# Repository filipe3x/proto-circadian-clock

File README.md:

# 🌅 Proto Circadian Clock

An ESP32-powered LED clock that simulates the natural solar light cycle to support healthy circadian rhythms. The display gradually transitions from warm red tones at sunrise/sunset to bright white at midday, mimicking natural daylight patterns.

## Features

- **Automatic Solar Simulation** - Real-time color temperature based on astronomical sun position
- **Red Light Therapy Mode** - Pure red light for evening relaxation
- **Multi-WiFi Support** - Connects to multiple configured networks with automatic fallback
- **Offline Operation** - Works without internet using RTC or internal clock
- **NTP Synchronization** - Keeps time accurate via internet time servers
- **Low Power** - Disconnects WiFi after sync to save energy
- **Startup Sound & Alerts** - Retro-style 8-bit chiptune sounds on boot (can be disabled via captive portal)

## Hardware Requirements

| Component | Specification |
|-----------|---------------|
| Microcontroller | ESP32 Dev Module (4MB Flash) |
| Display | P10 32×16 RGB LED Panel (HUB75, 1/4 scan, SMD3535) |
| RTC (Optional) | DS3231 module |
| Button | Momentary push button |
| Buzzer (Optional) | MLT-5030 piezo buzzer or similar (passive, 3V, 5×5mm) |
| Power | 5V 2A minimum |

## Wiring

### Pinout Absoluto ESP32 — Todos os GPIOs

```
┌─────────────────────────────────────────────────────────────────┐
│                    ESP32-WROOM-32E  PINOUT                      │
├───────┬──────────────┬──────────┬───────────────────────────────┤
│ GPIO  │ Função       │ Direção  │ Notas                        │
├───────┼──────────────┼──────────┼───────────────────────────────┤
│       │ ── HUB75 (Painel P10 RGB) ──                           │
│  4    │ LAT          │ Output   │ Latch                        │
│  5    │ C            │ Output   │ Row select bit 2             │
│ 12    │ G2           │ Output   │ Green lower                  │
│ 13    │ B2           │ Output   │ Blue lower                   │
│ 14    │ R2           │ Output   │ Red lower                    │
│ 15    │ OE           │ Output   │ Output Enable (active LOW)   │
│ 16    │ CLK          │ Output   │ Pixel clock                  │
│ 17    │ D            │ Output   │ Row select bit 3             │
│ 19    │ B            │ Output   │ Row select bit 1             │
│ 23    │ A            │ Output   │ Row select bit 0             │
│ 25    │ R1           │ Output   │ Red upper                    │
│ 26    │ G1           │ Output   │ Green upper                  │
│ 27    │ B1           │ Output   │ Blue upper                   │
├───────┼──────────────┼──────────┼───────────────────────────────┤
│       │ ── I2C (RTC + OLED) ──                                 │
│ 21    │ SDA          │ Bidi     │ DS3231 (0x68) + SSD1306 (0x3C) │
│ 22    │ SCL          │ Bidi     │ Barramento partilhado        │
├───────┼──────────────┼──────────┼───────────────────────────────┤
│       │ ── Input (partilhado — ver INPUT_MODE) ──              │
│ 34    │ ENC_A/BTN_A  │ Input    │ Pull-up 10kΩ ext. Encoder A ou Botão A │
│ 35    │ ENC_B/BTN_B  │ Input    │ Pull-up 10kΩ ext. Encoder B ou Botão B │
│ 36    │ BTN_L        │ Input    │ Pull-up 10kΩ ext. Exclusivo DevKit     │
│ 39    │ ENC_BTN/BTN_R│ Input    │ Pull-up 10kΩ ext. Enc Click ou Botão R │
├───────┼──────────────┼──────────┼───────────────────────────────┤
│       │ ── Outros ──                                           │
│  0    │ BOOT Button  │ Input    │ INPUT_PULLUP, modo cycle     │
│  2    │ LED_BUILTIN  │ Output   │ LED azul onboard             │
│ 18    │ BUZZER       │ Output   │ PWM → R 1kΩ → Q1 MMBT2222A  │
│ 33    │ VBUS_SENSE   │ Input    │ ADC1_CH5, deteção 20V        │
│  1    │ DEBUG TX     │ Output   │ UART0 TX (USB-UART)          │
│  3    │ DEBUG RX     │ Input    │ UART0 RX (USB-UART)          │
├───────┼──────────────┼──────────┼───────────────────────────────┤
│       │ ── Não disponíveis ──                                  │
│ 6-11  │ Flash SPI    │ —        │ Reservados internamente      │
│ 20    │ Não exposto  │ —        │ Indisponível na maioria dos devkits │
│ 24    │ Não existe   │ —        │ Não existe no ESP32          │
│ 28-31 │ Não expostos │ —        │ Não expostos em devkits      │
├───────┼──────────────┼──────────┼───────────────────────────────┤
│       │ ── Livre ──                                            │
│ 32    │ RESERVA      │ I/O      │ ADC1_CH4, touch — I2S DIN ou expansão │
└───────┴──────────────┴──────────┴───────────────────────────────┘
```

**Total: 28 GPIOs utilizados, 1 livre (GPIO 32), 10 indisponíveis.**

### Input Mode — GPIOs Partilhados

Os GPIOs 34, 35 e 39 servem dois modos de input (mesmo circuito elétrico):

```cpp
#define INPUT_MODE 0  // Click Wheel — encoder magnético AS5600 I2C (brilho + modo)
#define INPUT_MODE 1  // DevKit Buttons — 4 botões táteis (A/B/L/R)
```

Ver `DEVKIT_DISPLAY_BUTTONS.md` e `product/CLICK_WHEEL.md` para detalhes.

### ESP32 → P10 Panel (HUB75)

```
ESP32          P10 Panel
─────          ─────────
GPIO 25   →    R1
GPIO 26   →    G1
GPIO 27   →    B1
GPIO 14   →    R2
GPIO 12   →    G2
GPIO 13   →    B2
GPIO 23   →    A
GPIO 19   →    B
GPIO 5    →    C
GPIO 17   →    D
GPIO 4    →    LAT
GPIO 15   →    OE
GPIO 16   →    CLK
GND       →    GND
```

### I2C — RTC DS3231 + OLED SSD1306 (barramento partilhado)

```
ESP32          DS3231 (0x68)     SSD1306 (0x3C)
─────          ──────            ──────────────
GPIO 21   →    SDA          →    SDA
GPIO 22   →    SCL          →    SCL
3.3V      →    VCC          →    VCC
GND       →    GND          →    GND
```

> **Nota:** O OLED (SSD1306) é opcional, montado no verso da PCB (modo DevKit).
> Não conflitua com o RTC — endereços I2C diferentes.

### Button

```
GPIO 0    →    Button   →    GND
```

### Buzzer (Optional)

```
ESP32          Buzzer Circuit
─────          ──────────────
GPIO 18   →    R1 (1kΩ)   →   Base (NPN)
                               │
                               ├── Collector → Buzzer+ → 5V
                               │
                               └── Emitter → GND

D1 (1N4148) across Buzzer (cathode to +5V)
```

Recommended transistor: 2N2222 or BC547

**Note:** GPIO 18 is used because GPIO 6-11 are internally connected to the ESP32 flash SPI and unavailable.

## Software Dependencies

### ESP32 Board Package

In Arduino IDE, add this URL to **File → Preferences → Additional Board Manager URLs**:
```
https://espressif.github.io/arduino-esp32/package_esp32_index.json
```

Then install **esp32** by Espressif Systems via **Tools → Board → Boards Manager**.

> ⚠️ **Important:** Use **ESP32 Arduino 2.0.x** (tested with 2.0.14), NOT version 3.x.
> The ESP32-HUB75-MatrixPanel-I2S-DMA library has compatibility issues with ESP32 Arduino 3.x
> due to breaking changes in the ESP-IDF 5.x I2S and DMA APIs. Version 2.0.x uses ESP-IDF 4.4
> which provides stable support for HUB75 LED panels.

### Arduino Libraries

Install via **Sketch → Include Library → Manage Libraries**:

| Library | Version | Author | Description |
|---------|---------|--------|-------------|
| **ESP32-HUB75-MatrixPanel-I2S-DMA** | 3.0.x | mrcodetenz (mrfaptastic) | LED matrix driver |
| **RTClib** | 2.1.x | Adafruit | RTC DS3231 support |
| **Dusk2Dawn** | 1.0.x | DM Kishi | Solar calculations |
| **ESPAsyncWebServer** | 1.2.x | me-no-dev | Async web server for captive portal |
| **AsyncTCP** | 1.1.x | me-no-dev | Async TCP for ESP32 |

### Manual Installation

The P10 panel wrapper library (not in Library Manager):

```bash
cd ~/Arduino/libraries/
git clone https://github.com/filipe3x/P10_32x16_QuarterScan.git
```

## Configuration

### Location Settings

Edit these constants in `clock.ino`:

```cpp
// Your location (for solar calculations)
const float LATITUDE = 41.5362;    // Your latitude
const float LONGITUDE = -8.7813;   // Your longitude
const int TIMEZONE_OFFSET = 0;     // Hours from UTC

// Shift the solar cycle (e.g., -1 to wake up earlier)
const int SOLAR_OFFSET_HOURS = 1;
```

### WiFi Credentials

Copy `wifi_credentials.h.example` to `wifi_credentials.h` and add your networks:

```bash
cp wifi_credentials.h.example wifi_credentials.h
```

Then edit `wifi_credentials.h`:

```cpp
WiFiCredentials wifiNetworks[] = {
  {"YourNetwork1", "password1"},
  {"YourNetwork2", "password2"},
};
```

**Note:** `wifi_credentials.h` is ignored by git to keep your passwords private.

## Installation

1. Install [Arduino IDE](https://www.arduino.cc/en/software) with ESP32 board support
2. Install required libraries (see above)
3. Open `clock.ino`
4. Select board: **ESP32 Dev Module**
5. Set upload speed: **921600**
6. Configure your location and WiFi credentials
7. Upload to ESP32

## Usage

### Operating Modes

Press the button (GPIO 0) to cycle through modes:

| Mode | Description |
|------|-------------|
| **AUTO_SOLAR** | Automatic color based on sun position |
| **THERAPY_RED** | Constant red light for therapy/relaxation |
| **OFF** | Display turned off |

### Startup Sound

If buzzer is installed, the clock plays a retro-style 8-bit startup melody on boot. The sound can be:

- **Enabled/Disabled** via the captive portal web interface
- **Customized** with different chiptune melodies (NES/GameBoy style)
- **Future use** as alarm/notification sounds

The buzzer uses PWM to generate classic pulse wave tones with configurable duty cycles (12.5%, 25%, 50%) for authentic retro sound.

### Status Indicators (Boot)

| Color | Status |
|-------|--------|
| 🟢 Green | RTC + WiFi + NTP synced (perfect) |
| 🔵 Blue | WiFi + NTP synced (good) |
| 🟡 Yellow | RTC + WiFi, NTP failed |
| 🟣 Purple | RTC only, offline |
| 🟠 Orange | WiFi only, no valid time |
| 🔴 Red | Fully offline |

### Solar Color Schedule (Example: Winter, Portugal)

| Time | Elevation | Color | Brightness |
|------|-----------|-------|------------|
| 06:00 | -25° | Off | 0% |
| 07:30 | -12° | Deep red | 18% |
| 08:00 | -6° | Orange | 28% |
| 09:00 | 0° | Warm orange | 40% |
| 12:00 | 30° | Bright white | 100% |
| 18:00 | 0° | Warm orange | 40% |
| 21:00 | -12° | Deep red | 18% |
| 22:00 | -18° | Off | 0% |

## Troubleshooting

### Display not working
- Check 5V power supply (minimum 2A)
- Verify all HUB75 connections
- Ensure P10_32x16_QuarterScan library is installed

### RTC not detected
- System works without RTC (uses NTP)
- Check I2C connections (SDA=21, SCL=22)
- Verify 3.3V power (NOT 5V)
- Check CR2032 battery

### WiFi not connecting
- System works offline with RTC
- Check credentials in `wifiNetworks[]`
- Increase `WIFI_TIMEOUT_MS` for slow networks

### Wrong time/colors
- Verify `LATITUDE` and `LONGITUDE`
- Check `TIMEZONE_OFFSET` (0 for Portugal/UK)
- Adjust `SOLAR_OFFSET_HOURS` if needed

## Serial Monitor

Connect at **115200 baud** to see:
- Boot sequence and connectivity status
- Solar information (sunrise/sunset times)
- Elevation and color updates every 5 minutes
- Mode changes

## Roadmap

Potential future enhancements:

- **Dawn Simulator Mode** - Gradual wake-up light 30 min before alarm
- **Brightness Adjustment** - Manual or ambient sensor-based control
- **Web Interface** - Configuration via WiFi AP mode
- **Multiple Profiles** - Different settings per day of week
- **Home Assistant Integration** - MQTT control

## Authors

- **Filipe Marques** ([@filipe3x](https://github.com/filipe3x)) - Creator and maintainer
- **Claude** (Anthropic) - AI pair programming assistant

## License

MIT License - Feel free to use and modify.

## Contributing

Pull requests welcome! Please test on actual hardware before submitting.

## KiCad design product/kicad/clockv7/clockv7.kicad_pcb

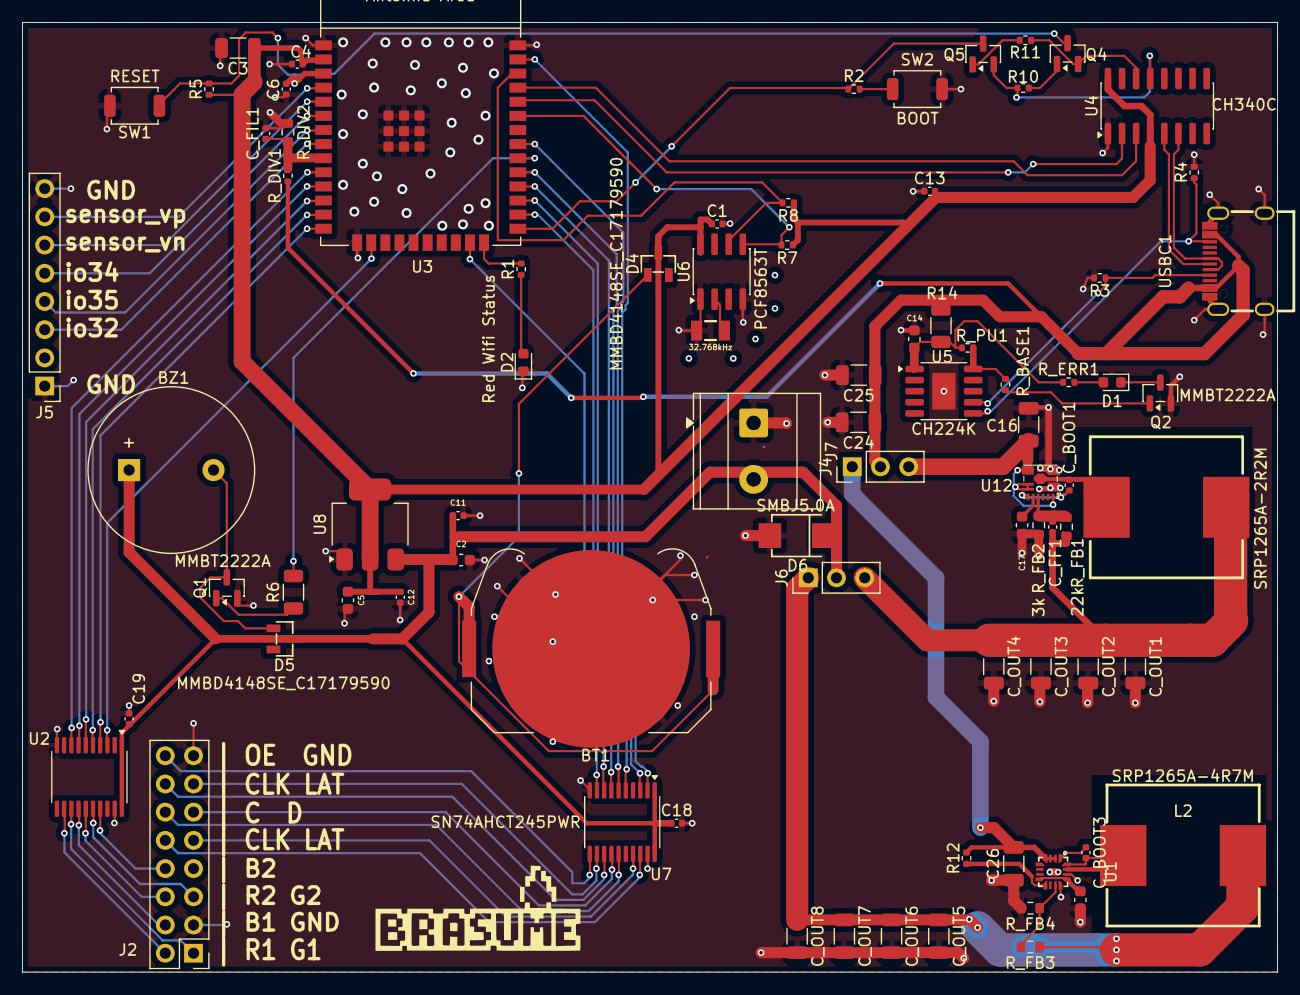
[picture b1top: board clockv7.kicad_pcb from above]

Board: 2 copper layers, 113.0 x 85.5 mm, 82 parts (0 on the bottom side), 76 nets.

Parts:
BT1: Battery_Cell; BatteryHolder_Keystone_3034_1x20mm
BZ1: Buzzer; Buzzer_14x9.5RM7.6
C1, C4, C6, C11, C12, C13, C18, C19: 100nF(50V); C_0402_1005Metric
C2: 10uF; C_0603_1608Metric
C3: 22uF(10V); C_1206_3216Metric
C5: 22uF; C_0603_1608Metric
C14, C17, C27: 1uF; C_0603_1608Metric
C16, C26: 10uF; C_1206_3216Metric
C24, C25: 22uF(25V); C_1206_3216Metric
C_BOOT1, C_BOOT3: 100nF(50V); C_0402_1005Metric
C_FF1: 22pF 50V; C_0402_1005Metric
C_FIL1: 100nF(50V); C_0402_1005Metric
C_OUT1, C_OUT2, C_OUT3, C_OUT4, C_OUT5, C_OUT6, C_OUT7, C_OUT8: 22uF(25V); C_1206_3216Metric
D1: LED_ERR; LED_0603_1608Metric
D2: Red Wifi Status; LED_0603_1608Metric
D4, D5: MMBD4148SE_C17179590; SOT-23-3_L2.9-W1.3-P0.95-LS2.4-BR
D6: SMBJ5.0A; SMB_L4.6-W3.6-LS5.4-RD
J2: GPIO +5V; PinHeader_2x08_P2.54mm_Vertical
J4, J6: Conn_01x03; PinHeader_1x03_P2.54mm_Vertical
J5: GPIO +3V3; PinHeader_1x08_P2.54mm_Vertical
J7: 3.5mm; TerminalBlock_Phoenix_MKDS-3-2-5.08_1x02_P5.08mm_Horizontal
L1: SRP1265A-2R2M; IND-SMD_L13.5-W12.5
L2: SRP1265A-4R7M; IND-SMD_L13.5-W12.5
Q1, Q2, Q4, Q5: MMBT2222A; SOT-23
R1: 330R; R_0402_1005Metric
R2: 100R; R_0402_1005Metric
R3, R4: 5.1k; R_0402_1005Metric
R5, R10, R11: 10k; R_0402_1005Metric
R6, R14: 1K; R_1206_3216Metric
R7, R8: 4.7k; R_0402_1005Metric
R12: 47k; R_0402_1005Metric
R_BASE1: 10k; R_0402_1005Metric
R_DIV1: 47k; R_0402_1005Metric
R_DIV2: 5.6k; R_0603_1608Metric
R_ERR1: 330R; R_0402_1005Metric
R_FB1, R_FB3: 22k; R_0603_1608Metric
R_FB2, R_FB4: 3k; R_0603_1608Metric
R_PU1: 10k; R_0402_1005Metric
SW1: RESET; SW_SPST_TS-1088-xR025
SW2: BOOT; SW_SPST_TS-1088-xR025
U1: SY8388ARHC; QFN-16_L2.5-W2.5-P0.45-TL-EP0.6
U2, U7: SN74AHCT245PWR; TSSOP-20_4.4x6.5mm_P0.65mm
U3: ESP32-WROOM-32EN8 (8MB); ESP32-WROOM-32E
U4: CH340C; SOIC-16_3.9x9.9mm_P1.27mm
U5: CH224K; SSOP-10-1EP_3.9x4.9mm_P1mm_EP2.1x3.3mm
U6: PCF8563T; SOIC-8_3.9x4.9mm_P1.27mm
U8: AMS1117-3.3; SOT-223-3_TabPin2
U12: SY8368AQQC; QFN-12_L3.0-W3.0-P0.45-TL-EP
USBC1: TYPE-C-31-M-12; USB-C_SMD-TYPE-C-31-M-12_1
Y1: 32.768kHz; Crystal_SMD_3.2x1.5mm

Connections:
5V_BUCK1: C_FF1.1, C_OUT1.1, C_OUT2.1, C_OUT3.1, C_OUT4.1, J6.3, L1.2, R_FB1.1
5V_BUCK2: C_OUT5.1, C_OUT6.1, C_OUT7.1, C_OUT8.1, J6.1, L2.2, R_FB3.1
5V_OUT: BZ1.1 (+), C2.1, C11.1, C18.1, C19.2, D5.3, D6.1 (K), J6.2, J7.2, U2.1 (DIR), U2.20 (VCC), U7.1 (DIR), U7.20 (VCC), U8.3 (VI)
20V_BUCK1: C16.1, J4.3, U12.4 (IN), U12.5 (IN), U12.6 (IN), U12.12 (EN)
20V_BUCK2: C26.2, J4.1, R12.2, U1.2 (IN), U1.3 (IN), U1.4 (IN)
20V_OUT: C24.1, C25.1, J4.2, R14.2, R_DIV1.1, USBC1.A4B9 (VBUS), USBC1.B4A9 (VBUS)
+3V3: C1.1, C3.1, C4.1, C5.1, C12.1, C13.2, D4.3, R5.1, R7.1, R8.1, U3.2 (VDD), U4.4 (V3), U4.16 (VCC), U6.8 (VDD), U8.2 (VO)
A: U3.37 (IO23), U7.2 (A1)
A_HUB75: J2.10, U7.18 (B1)
B: U3.31 (IO19), U7.3 (A2)
B1: U2.6 (A5), U3.12 (IO27)
B1_HUB75: J2.4, U2.14 (B5)
B2: U2.3 (A2), U3.16 (IO13)
B2_HUB75: J2.8, U2.17 (B2)
BOOT: Q5.3 (C), R2.1, U3.25 (IO0)
BUZZER: R6.2, U3.30 (IO18)
B_HUB75: J2.9, U7.17 (B2)
C: U3.29 (IO5), U7.5 (A4)
CC1: R3.1, U5.7 (CC1), USBC1.A5 (CC1)
CC2: R4.1, U5.6 (CC2), USBC1.B5 (CC2)
CLK: U3.27 (IO16), U7.7 (A6)
CLK_HUB75: J2.14, U7.13 (B6)
C_HUB75: J2.12, U7.15 (B4)
D: U3.28 (IO17), U7.6 (A5)
D+: U4.5 (UD+), USBC1.A6 (DP1), USBC1.B6 (DP2)
D-: U4.6 (UD-), USBC1.A7 (DN1), USBC1.B7 (DN2)
DTR: Q5.2 (E), R10.1, U4.13 (~DTR)
D_HUB75: J2.11, U7.14 (B5)
EN: C6.2, Q4.3 (C), R5.2, SW1.1 (A), U3.3 (EN)
FB1: C_FF1.2, R_FB1.2, R_FB2.1, U12.9 (FB)
FB2: R_FB3.2, R_FB4.1, U1.11 (FB)
G1: U2.7 (A6), U3.11 (IO26)
G1_HUB75: J2.1, U2.13 (B6)
G2: U2.4 (A3), U3.14 (IO12)
G2_HUB75: J2.5, U2.16 (B3)
GND: BT1.2 (-), C1.2, C2.2, C3.2, C4.2, C5.2, C6.1, C11.2, C12.2, C13.1, C14.2, C16.2, C17.2, C18.2, C19.1, C24.2, C25.2, C26.1, C27.1, C_FIL1.2, C_OUT1.2, C_OUT2.2, C_OUT3.2, C_OUT4.2, C_OUT5.2, C_OUT6.2, C_OUT7.2, C_OUT8.2, D2.1 (K), D6.2 (A), J2.3, J2.15, J5.1, J5.8, J7.1, Q1.2 (E), Q2.2 (E), R3.2, R4.2, R_DIV2.1, R_FB2.2, R_FB4.2, SW1.2 (B), SW2.2 (B), U1.12 (BYP), U1.14 (GND), U1.17 (GND), U2.10 (GND), U2.19 (~OE), U3.1 (GND), U3.15 (GND), U3.38 (GND), U3.39 (GND), U4.1 (GND), U5.11 (GND), U6.1 (OSCI), U6.4 (VSS), U7.10 (GND), U7.19 (~OE), U8.1 (GND), U12.1 (GND), U12.3 (GND), USBC1.1 (EH), USBC1.2 (EH), USBC1.3 (EH), USBC1.4 (EH), USBC1.A1B12 (GND), USBC1.B1A12 (GND), Y1.1
L1: C_BOOT1.2, L1.1, U12.2 (LX)
L2: C_BOOT3.2, L2.1, U1.15 (LX), U1.16 (LX)
LAT: U3.26 (IO4), U7.8 (A7)
LAT_HUB75: J2.13, U7.12 (B7)
unnamed: BT1.1 (+), D4.1
unnamed: BZ1.2 (-), D5.1, Q1.3 (C)
unnamed: D1.2 (A), R_ERR1.2
unnamed: D1.1 (K), Q2.3 (C)
unnamed: D2.2 (A), R1.1
unnamed: J5.3, U3.8 (IO32)
unnamed: J5.4, U3.7 (IO35)
unnamed: J5.5, U3.6 (IO34)
unnamed: J5.6, U3.5 (SENSOR_VN)
unnamed: J5.7, U3.4 (SENSOR_VP)
unnamed: Q1.1 (B), R6.1
unnamed: Q2.1 (B), R_BASE1.2
unnamed: Q4.1 (B), R10.2
unnamed: Q5.1 (B), R11.2
unnamed: R2.2, SW2.1 (A)
unnamed: C_BOOT3.1, U1.1 (BS)
unnamed: R12.1, U1.9 (EN)
unnamed: C27.2, U1.8 (MODE), U1.13 (VCC)
unnamed: R1.2, U3.24 (IO2)
unnamed: R_BASE1.1, R_PU1.2, U5.10 (PG)
unnamed: C14.1, R14.1, R_ERR1.1, R_PU1.1, U5.1 (VDD)
unnamed: U6.2 (OSCO), Y1.2
unnamed: C_BOOT1.1, U12.7 (BS)
unnamed: C17.1, U12.8 (VCC)
OE: U3.23 (IO15), U7.9 (A8)
OE_HUB75: J2.16, U7.11 (B8)
R1: U2.8 (A7), U3.10 (IO25)
R1_HUB75: J2.2, U2.12 (B7)
R2: U2.5 (A4), U3.13 (IO14)
R2_HUB75: J2.6, U2.15 (B4)
RTS: Q4.2 (E), R11.1, U4.14 (~RTS)
RX: U3.35 (TXD0/IO1), U4.3 (RXD)
SCA: R7.2, U3.33 (IO21), U6.5 (SDA)
SCL: R8.2, U3.36 (IO22), U6.6 (SCL)
TX: U3.34 (RXD0/IO3), U4.2 (TXD)
VBUS_SENSE: C_FIL1.1, R_DIV1.2, R_DIV2.2, U3.9 (IO33)

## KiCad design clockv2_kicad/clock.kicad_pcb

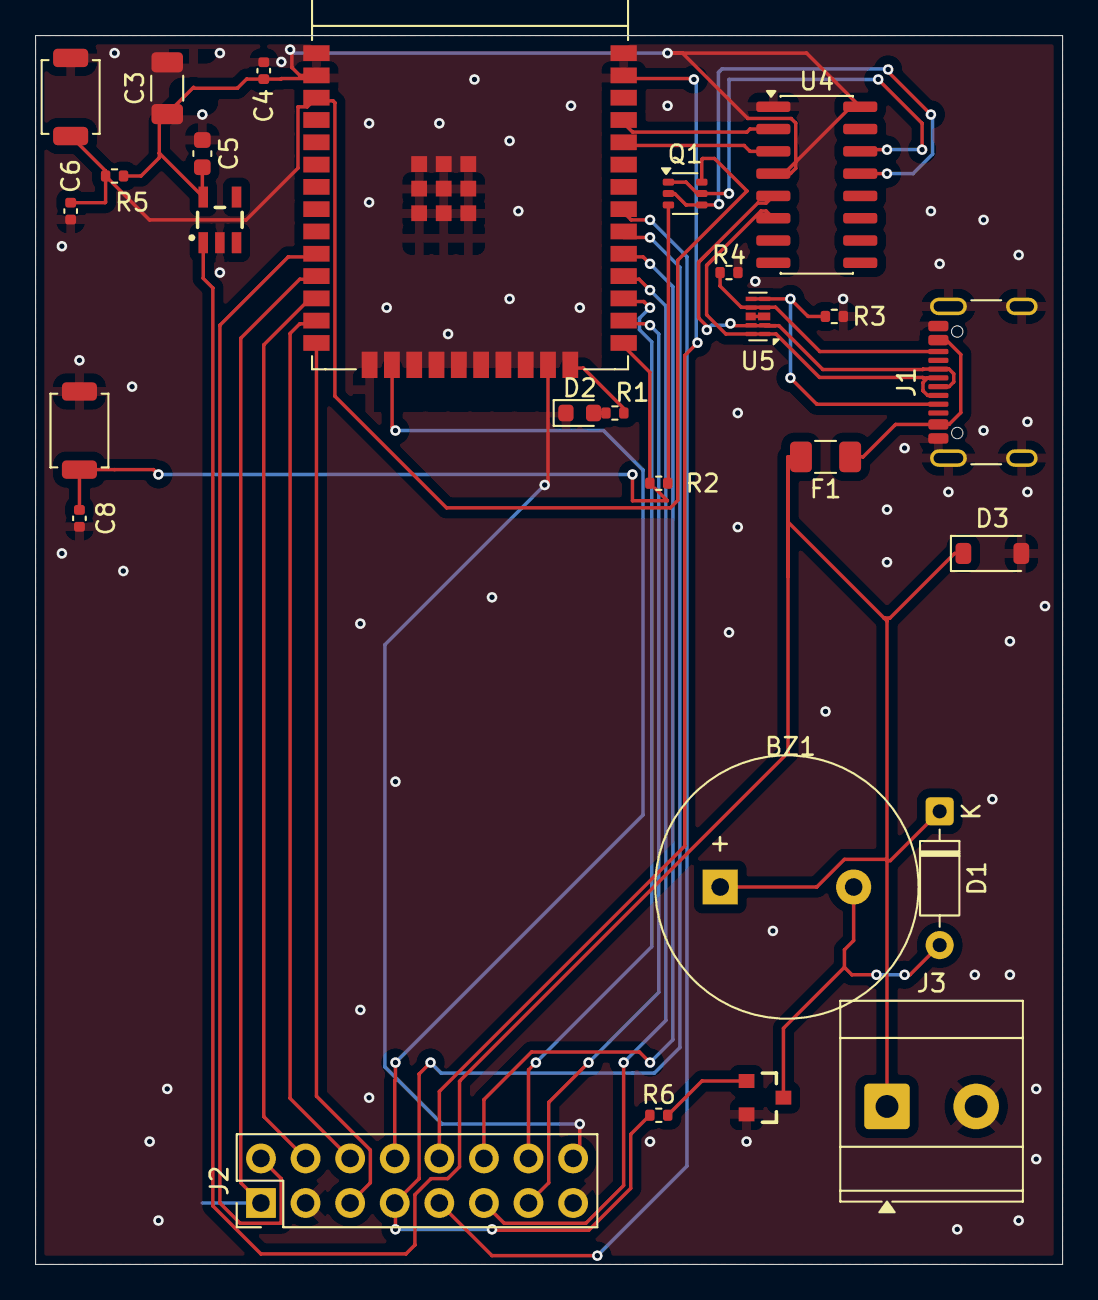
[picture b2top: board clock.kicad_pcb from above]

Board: 2 copper layers, 58.5 x 70.0 mm, 27 parts (0 on the bottom side), 33 nets.

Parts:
BZ1: Buzzer; Buzzer_14x9.5RM7.6
C3: C_Small 22uF(10V); C_1206_3216Metric
C4, C6, C8: 100nF (50V); C_0402_1005Metric
C5: 10uF; C_0603_1608Metric
D1: 1N4148; D_DO-35_SOD27_P7.62mm_Horizontal
D2: Red Wifi Status; LED_0603_1608Metric
D3: D_TVS; D_SOD-123
F1: Polyfuse; Fuse_1206_3216Metric
J1: USB_C_Receptacle_USB2.0_16P; USB_C_Receptacle_GCT_USB4105-xx-A_16P_TopMnt_Horizontal
J2: Conn_02x08_Odd_Even; PinHeader_2x08_P2.54mm_Vertical
J3: Barrier Terminal; TerminalBlock_Phoenix_MKDS-3-2-5.08_1x02_P5.08mm_Horizontal
Q1: UMH3N; SOT-363_SC-70-6
Q2: MMBT2222A; SOT23-3
R1: 330R; R_0402_1005Metric
R2: 100R; R_0402_1005Metric
R3, R4: 5.1k; R_0402_1005Metric
R5: R 10k; R_0402_1005Metric
R6: 1K; R_0402_1005Metric
SW1: RESET; SW_SPST_TS-1088-xR025
SW2: BOOT; SW_SPST_TS-1088-xR025
U3: ESP32-WROOM-32E (8MB); ESP32-WROOM-32E
U4: CH340C; SOIC-16_3.9x9.9mm_P1.27mm
U5: D3V3XA4B10LP; Diodes_UDFN-10_1.0x2.5mm_P0.5mm
U6: AP2112K-3.3; SOT23-5

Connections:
5VV: BZ1.1 (+), D1.1 (K), D3.1 (A1), F1.2, J3.1, U6.1 (VIN), U6.3 (EN)
+3V3: C3.1, C4.1, C5.1, R5.1, U3.2 (VDD), U4.4 (V3), U4.16 (VCC), U6.5 (VOUT)
A: J2.10, U3.37 (IO23)
B: J2.9, U3.31 (IO19)
B1: J2.4, U3.12 (IO27)
B2: J2.8, U3.16 (IO13)
BOOT: Q1.3 (C2), R2.1, U3.25 (IO0)
BUZZER: J2.7, R6.2, U3.30 (IO18)
C: J2.12, U3.29 (IO5)
CLK: J2.14, U3.27 (IO16)
D: J2.11, U3.28 (IO17)
D+: J1.A6 (D+), J1.B6 (D+), U4.5 (UD+), U5.2, U5.9 (NC)
D-: J1.A7 (D-), J1.B7 (D-), U4.6 (UD-), U5.1, U5.10 (NC)
DTR: Q1.2 (B1), Q1.4 (E2), U4.13 (~DTR)
EN: C6.2, Q1.6 (C1), R5.2, SW1.1 (A), U3.3 (EN)
G1: J2.1, U3.11 (IO26)
G2: J2.5, U3.14 (IO12)
GND: C3.2, C4.2, C5.2, C6.1, C8.1, D2.1 (K), D3.2 (A2), J1.A1 (GND), J1.A12 (GND), J1.B1 (GND), J1.B12 (GND), J1.S1 (SHIELD), J2.3, J2.15, J3.2, Q2.2 (E), R3.2, R4.2, SW1.2 (B), SW2.2 (B), U3.1 (GND), U3.15 (GND), U3.38 (GND), U3.39 (GND), U4.1 (GND), U5.3 (VSS), U5.8 (VSS), U6.2 (GND)
LAT: J2.13, U3.26 (IO4)
unnamed: BZ1.2 (-), Q2.3 (C)
unnamed: D2.2 (A), R1.1
unnamed: F1.1, J1.A4 (VBUS), J1.A9 (VBUS), J1.B4 (VBUS), J1.B9 (VBUS)
unnamed: J1.A5 (CC1), R3.1, U5.5, U5.6 (NC)
unnamed: J1.B5 (CC2), R4.1, U5.4, U5.7 (NC)
unnamed: Q2.1 (B), R6.1
unnamed: C8.2, R2.2, SW2.1 (A)
unnamed: R1.2, U3.24 (IO2)
OE: J2.16, U3.23 (IO15)
R1: J2.2, U3.10 (IO25)
R2: J2.6, U3.13 (IO14)
RTS: Q1.1 (E1), Q1.5 (B2), U4.14 (~RTS)
RX: U3.34 (RXD0/IO3), U4.3 (RXD)
TX: U3.35 (TXD0/IO1), U4.2 (TXD)

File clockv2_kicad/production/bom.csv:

Designator,Footprint,Quantity,Value,LCSC Part #
BZ1,Buzzer_12x9.5RM7.6,1,Buzzer,C252948
C3,1206,1,C_Small 22uF(10V),C12891
"C4, C6, C8",0402,3,100nF (50V),C307331
C5,0603,1,10uF,C19702
D1,D_DO-35_SOD27_P7.62mm_Horizontal,1,1N4148,C84410
D2,0603,1,Red Wifi Status,C2286
D3,D_SOD-123,1,D_TVS,C123799
F1,1206,1,Polyfuse,C106264
J1,USB_C_Receptacle_GCT_USB4105-xx-A_16P_TopMnt_Horizontal,1,USB_C_Receptacle_USB2.0_16P,C3020560
J2,PinHeader_2x08_P2.54mm_Vertical,1,Conn_02x08_Odd_Even,C68234
J3,TerminalBlock_Phoenix_MKDS-3-2-5.08_1x02_P5.08mm_Horizontal,1,Barrier Terminal,C474881
Q1,SOT-363_SC-70-6,1,UMH3N,C62892
Q2,SOT23-3,1,MMBT2222A,C916372
R1,0402,1,330R,C25104
R2,0402,1,100R,C106232
"R3, R4",0402,2,5.1k,C25905
R5,0402,1,R 10k,C25744
R6,0402,1,1K,C106235
SW1,SW_SPST_TS-1088-xR025,1,RESET,C720477
SW2,SW_SPST_TS-1088-xR025,1,BOOT,C720477
U3,ESP32-WROOM-32E,1,ESP32-WROOM-32E (8MB),C701342
U4,SOIC-16_3.9x9.9mm_P1.27mm,1,CH340C,C84681
U5,Diodes_UDFN-10_1.0x2.5mm_P0.5mm,1,D3V3XA4B10LP,C1980462
U6,SOT23-5,1,AP2112K-3.3,C82942

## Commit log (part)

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2025-12-25 Add Claude.md with project documentation
    Provides context for AI assistants including tech stack, hardware
    pinout, architecture overview, and development guidelines.
2025-12-25 Add comprehensive product commercialization strategy
    Include market analysis, pricing models, partnership opportunities,
    go-to-market strategy, financial projections, and action roadmap
    for transforming the prototype into a mass-market product.
2025-12-26 Add instant mode sync and collision-free ACKs
    - Broadcast mode change immediately on button press (before animation)
    - Any device can trigger mode sync (not just master)
    - ACKs use slot-based backoff to prevent collision storms
    - Receivers apply mode instantly without animation for fast feedback
    - Add MeshSync.md documentation explaining the protocol
2025-12-26 Implement captive portal for mobile configuration
    Add a web-based configuration system that allows users to set up the
    clock via their smartphone without installing any apps. Features:
    - Auto-detect first boot and start captive portal if no config exists
    - Beautiful dark-themed UI matching the project's design language
    (lavender, amber, mint accents on deep dark background)
    - Configure dual WiFi networks (primary + backup)
2025-12-26 Add comprehensive auto_solar module documentation
    Document the solar gradient calculation algorithms with:
    - NOAA solar position algorithm with mathematical formulas
    - Tanner Helland color temperature to RGB conversion
    - Elevation-to-color mapping based on astronomical definitions
    - Scientific references for circadian impact
    - Future improvement proposals including:
2025-12-26 setup screen
2025-12-26 Add ESP32 power supply documentation
    Document strategies for safely powering the ESP32 from a shared
    5V DC power supply with the P10 panel, including protection circuits
    (Schottky diode, PTC fuse, filter capacitors) and AliExpress shopping lists.
2025-12-26 Fix compilation errors in prepareForRestart()
    - Remove duplicate default argument (keep only in header)
    - Replace getBrightness() with configBrightness variable
2025-12-26 Fix scroll issue when using brightness slider on mobile
2025-12-27 Improve brightness validation and adopt configBrightness in red therapy
    - Add constrain(10, 255) validation on /save endpoint to prevent
    invalid brightness values from being stored in NVS
    - Use configBrightness in displayTherapyRed() instead of hardcoded 100,
    capped at 240 to prevent visual discomfort and excessive 5V consumption
2025-12-29 Update POWER_SUPPLY_v2.md based on MatrixPortal S3 schematic analysis
    - Replace AMS1117 with AP2112K-3.3 (better dropout, enable pin, used by Adafruit)
    - Add power indicator LEDs section (5V and 3.3V status LEDs)
    - Add BOM for 3.3V regulator and LEDs
    - Add reference to MatrixPortal S3 schematic analysis findings
    - Confirm MatrixPortal S3 uses simple 5V passthrough (no PD controller)
    - Update version to 2.1
2025-12-30 Update PCB design guide with USB-C power and protection from POWER_SUPPLY_v2
    - Add USB-C Power Delivery architecture (Strategy A: 5V direct, Strategy B: High voltage + Buck)
    - Update section 1.2 with AP2112K LDO, IP2721 PD controller, MP1584EN buck converter
    - Add comprehensive USB-C protection in section 1.3 (D3V3XA4B10LP for D+/D-/CC, SMBJ5.0A for VBUS)
    - Add screw terminal reverse polarity protection with Si2301CDS P-MOSFET
    - Add inrush current limiting section 2.6 (NTC thermistor and P-MOSFET soft-start)
    - Add terminal protection section 2.7
2026-01-01 Create separate v2.1 file and revert PCB_DESIGN_GUIDE to v2.0
    - Created product/PCB_DESIGN_GUIDE_v2.1.md with buzzer feature (complete version)
    - Reverted product/PCB_DESIGN_GUIDE.md to v2.0 (USB-C power, no buzzer)
    - v2.1 preserves all buzzer documentation for future reference
    - v2.0 maintains clean USB-C power protection baseline
2026-01-02 Fix screw terminal LCSC part number
    C430646 was wrong (5-pin DORABO) - corrected to C474881 (KF301-5.0-2P 2-pin)
    Updated: COMPONENT_ALTERNATIVES.md, PCB_DESIGN_GUIDE.md, POWER_SUPPLY_v2.md
2026-01-02 Update RTC documentation with correct RST pin info
    - BOM_VERIFIED.md: Add RTC components section with LCSC codes
    (DS3231SN, 4.7kΩ pull-ups, 100nF bypass, CR2032 holder)
    - PCB_DESIGN_GUIDE.md: Add section 2.7 with complete RTC circuit
    - Correct pinout and schematic
    - Note: ~RST has internal 50kΩ pull-up (no external needed)
    - GPIO mappings for ESP32 Dev and Matrix Portal S3
2026-01-03 Add PCF8563T as Preferred Extended RTC alternative
    - Section 1.1: Add PCF8563T (C7563) as cost-optimized RTC option
    - Preferred Extended = $0 loading fee on JLCPCB Economic PCBA
    - Comparison table: DS3231SN vs PCF8563T
    - Total savings: ~€2 (component) + $3 (fee) = ~€5/lot
    - Section 2.7: Add complete PCF8563T circuit
    - SOIC-8 pinout diagram
2026-01-04 Add D4 battery backup diode and update PCF8563T documentation
    - Add D4 (MMBD4148SE) for RTC battery backup circuit
    - Update D3 with verified C20615788 (H7VN10B TVS) specs
    - Add complete PCF8563T SOIC-8 pinout and connection guide
    - Document battery backup circuit: D4 as OR diode between VDD and CR2032
    - Clarify which pins can be left NC (INT, CLKOUT)
2026-01-13 Add PCB debug checklist for new boards
    Checklist to verify PCB functionality when receiving from manufacturer:
    - Visual inspection
    - Continuity tests (shorts detection)
    - Power rail verification
    - USB recognition
    - ESP32 bootloader response
2026-01-14 Update PSU docs with J_MODE 3-pin jumper for bypass
    - Replace J_BYPASS (2-pin) with J_MODE (1x3) for mode selection
    - Document bypass limitations (Buck dropout with 5V input)
    - Add detailed J_MODE wiring and operation modes
    - Update KiCad guide with new jumper connections
    - Clarify IP2721 behavior with basic USB 5V chargers
2026-01-14 Mark D1 TVS as Extended (Promo) - no extra fee
2026-01-15 Add complete Block 2 KiCad wiring guide
    Step-by-step instructions for SY8368AQQC Buck Converter:
    - 13 detailed connection steps with diagrams
    - VIN, EN, BOOT, SS, MODE, GND connections
    - SW to inductor and output capacitors
    - Critical feedback divider (22k/3k for 5V)
    - Complete verification checklist
2026-01-16 Update component references to match KiCad schematic
    Changed component designators in documentation to match actual KiCad refs:
    - U1 → U10 (IP2721 PD Trigger)
    - U2 → U12 (SY8368AQQC Buck)
    - Q1 → Q3 (AO3404A MOSFET)
    - D1/D2 → D3/D4 (TVS protection)
    - J2 → J3 (Barrier Terminal)
2026-01-18 Add brightness cap for Matrix Portal S3 PSU protection
    - Add MAX_BRIGHTNESS_CAP (80% / 204) for Matrix Portal S3 to ensure
    power consumption stays below 25W PSU limit (panel = 28W @ 100%)
    - Add setSafeBrightness() helper that applies cap before setting brightness
    - Apply cap to all setBrightness8 calls in clock.ino
    - Cap brightness levels array in button handler
    - Show power info at boot for Matrix Portal S3
2026-02-01 Add SY8368 Silergy drop-in FCCM investigation and VIN pin analysis
    Document investigation into Silergy alternatives with forced PWM/FCCM
    mode in the same QFN3x3-12 package as SY8368AQQC. No confirmed drop-in
    exists - chips with MODE pin (SY8388A, SY21243A) use different packages.
    Confirms TPS56838 decision remains correct. Also documents that all 3
    VIN pins (4,5,6) must be connected and layout strategy for 2-layer boards.
    https://claude.ai/code/session_017xG7iBcskJSNfEVwndU9qk
2026-02-03 Use 0603 Basic parts for VBUS voltage divider
    Switch from 0402 (Extended) to 0603 (Basic) to reduce JLCPCB
    assembly cost:
    - R_DIV1: 47kΩ C25819 (0603 Basic)
    - R_DIV2: 5.6kΩ C23189 (0603 Basic)
    https://claude.ai/code/session_017xG7iBcskJSNfEVwndU9qk
2026-02-05 Fix R_VBUS: 10kΩ 0402 (voltage detection, not power supply)
    CH224K VBUS pin (pin 8) is high-impedance voltage detection input,
    NOT the power supply input. Updated to match WCH reference schematic:
    - R_VBUS = 10kΩ (was 1kΩ): high impedance for BC1.2/QC detection
    - Package: 0402 (was 0603): 28mW dissipation well within rating
    - Power calc: (20V-3.3V)/10kΩ = 1.67mA → 28mW
    The CH224K internal LDO is powered through its own circuitry,
2026-03-03 Fix VBUS_SENSE_PIN: GPIO33 (IO33/ADC1_CH5), not GPIO9
    PCB connects voltage divider to IO33 as documented in POWER_SUPPLY_v3.md.
    GPIO9 was incorrect — caused 0V readings.
    https://claude.ai/code/session_017xG7iBcskJSNfEVwndU9qk
2026-03-05 fix(psu): corrigir refs KiCad — R_FB3/R_FB4, C_OUT5-8 (22µF 25V)
    - Renomear R_FB1/R_FB2 → R_FB3/R_FB4 para coincidir com KiCad
    - Corrigir C_OUT de 3× 22µF/10V (1206) para 4× 22µF/25V (1210)
    para coincidir com C_OUT5-8 no psu.kicad_sch
    - Adicionar explicação funcional do divisor de feedback
    - Adicionar explicação funcional dos C_OUT (ripple, transitória, ESR)
    https://claude.ai/code/session_01MMfczentGLp3AjPWcUBdjF
2026-03-05 Remove BUCK1 (L1=2.2µH), keep only BUCK2 (L2=4.7µH) — PFM noise fix
    BUCK1 was removed from the design due to Pulse Skipping (PFM) noise.
    Only BUCK2 with L2 (SRP1265A-4R7M, 4.7µH 16A) is assembled.
    Updated:
    - POWER_SUPPLY.md v4.1→v4.2: all L1→L2 refs, layout rules, BOM
    - Recalculated ripple: 1.33A p-p inductor, 3.3mV total (was 7mV with 2.2µH)
    - Thermal: L2 DCR=7.4mΩ → 0.47W (was 0.3W), Isat=16A still >>8A
2026-03-07 fix(uart): corrige ligação V3 do CH340C e documenta modo 3.3V
    O pino V3 do CH340C estava documentado como → GND, o que está errado
    em modo 3.3V. Quando VCC=3.3V, V3 deve ligar a VCC para bypasasr o
    LDO interno — ligá-lo a GND causaria instabilidade no regulador.
    Adicionada explicação do motivo para usar modo 3.3V (não 5V):
    os pinos GPIO3/GPIO1 do ESP32 não são 5V-tolerant, pelo que ligar
    TXD do CH340C a 5V destruiria o ESP32 sem level-shifter intermédio.
2026-03-10 hub75 footprint and pins
2026-03-11 docs: U9 MAX98357AEWL+T como DNP placeholder para clockv8
    - BOM_VERIFIED.md: adicionar U9 (C2682619) na secção DNP — não conta
    no BOM nem na montagem JLCPCB
    - SPEAKER.md: documentar footprint correto Maxim_WLP-9_1.595x1.415
    (KiCad default, dimensões exactas do datasheet) vs alternativas
    - Footprint a usar no KiCad: Maxim_WLP-9_1.595x1.415_Layout3x3_P0.4mm_Ball0.27mm_Pad0.25mm_NSMD
    https://claude.ai/code/session_01XzuFyfAuaeVs8TmypMn2JM
2026-03-12 Simplify click wheel: keep BOOT as mode button, encoder only for brightness
    - Remove CENTER_BTN_PIN — BOOT (GPIO0) stays as mode change button
    - Encoder A/B moved to GPIO 34/35 (input-only, need external 10kΩ pullup)
    - GPIO 32 freed (used by MAX98357A I2S DIN)
    - Removed all centerBtn ISR/handler code
    https://claude.ai/code/session_01BLfotpFbp7pGKfWjcLfbA3
2026-03-28 Document shared GPIO pins between click wheel and devkit buttons
    GPIOs 34, 35, 39 are shared between the click wheel encoder and the
    devkit tactile buttons (A/B/R). The electrical circuit is identical
    (input-only + 10k pull-up + active LOW), so the same PCB pads and
    resistors serve both configurations. A compile-time INPUT_MODE flag
    selects the firmware. GPIO 36 remains exclusive to devkit (BTN_L).
    Updated both DEVKIT_DISPLAY_BUTTONS.md and product/CLICK_WHEEL.md
2026-03-29 Replace ITR8307 optical encoder with AS5600 magnetic encoder for click wheel
    After further evaluation, the AS5600 I2C magnetic encoder replaces the
    2x ITR8307 optical sensor + slotted disc design. Benefits: single chip
    on I2C bus (0x36), 12-bit native resolution (4096 positions), no
    precision mechanical parts, and frees GPIO 34/35 in click wheel mode.
    Updated: CLICK_WHEEL.md (full rewrite), CLAUDE.md (BOM, pinout, input
    mode table, tech stack), DEVKIT_DISPLAY_BUTTONS.md (sections 6/7/8/9),
